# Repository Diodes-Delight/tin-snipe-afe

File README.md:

# Tin Snipe Analog Frontend

Tin Snipe is a multimeter for the hardware engineer on the go.

More to follow.

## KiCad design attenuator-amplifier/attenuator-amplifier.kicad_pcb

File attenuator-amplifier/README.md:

# Attenuator and Amplifier

This project is the attenuator and the amplifier portion of the AFE.
The attenuation is 1000:1, 100:1 and 10:1 while the amplification can be set to 1x, 10x and 100x with the 1x being the buffer
configuration which is used for signals which are either exactly in range or for attenuated signals which should also be buffered
so as to not load the input source too much.

## Building the firmware

The board itself does not contain any microcontrollers, but for testing a TI LaunchPad LP-MSPM0C1104 is used. This board was chosen for its low cost, wide availability from distributors and on board debugger.

For building and running, [Code Composer Studio](https://www.ti.com/tool/CCSTUDIO) and the [LP-MSPM0C1104](https://www.ti.com/tool/LP-MSPM0C1104) are necessary.
To build and run the firmware, simply open this folder in ccstudio and either use the Menu Run->Flash Project or Debug Project. ccstudio automatically detects the plugged in LaunchPad and can debug and flash the system from within the IDE.

The connectors J4 and J5 should be connected with cables in order to the following pins:

```
J4:

1 - PA25
2 - PA26
3 - PA17
4 - PA6
5 - PA11
6 - PA24
7 - PA4
8 - GND

J5:

1 - read below
2 - 3.3V
2 - unused for now
4 - GND
```

Warning! connect pin 1 to 5V only after the board has been flashed at least once! This is to prevent it being in an undefined state and potentially damaging the relays.

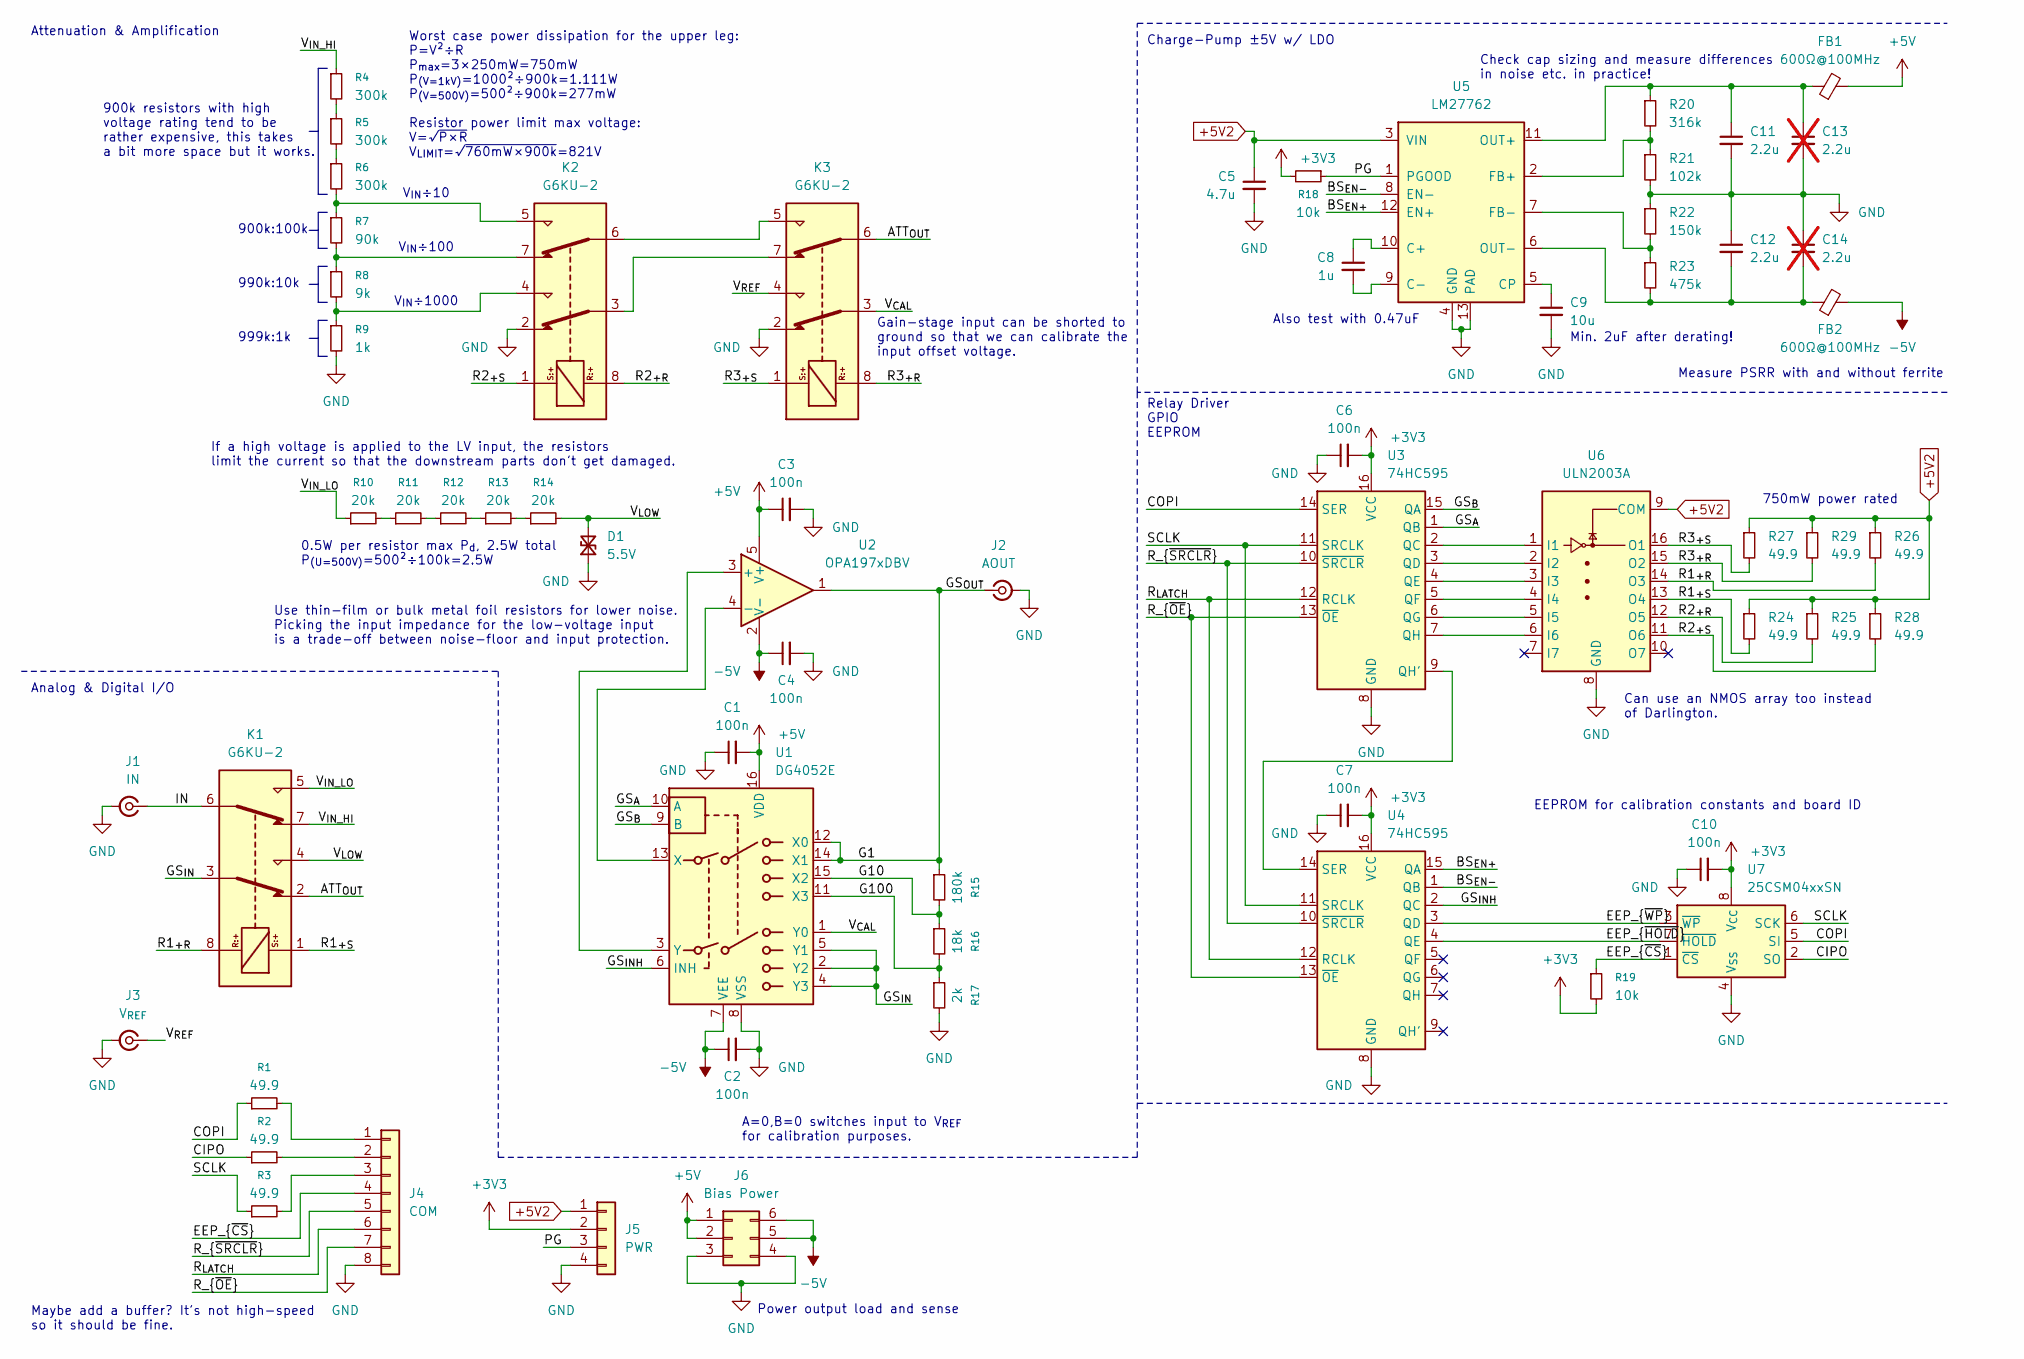
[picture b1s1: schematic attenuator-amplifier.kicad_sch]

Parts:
C1, C2, C3, C4, C6, C7, C10: 100n; C_0402_1005Metric; MPN FN15X104K500PKG
C5: 4.7u; C_0603_1608Metric; MPN TCC0603X7R475K100CT
C8: 1u; C_0603_1608Metric; MPN CGA0603X7R105K250JT
C9: 10u; C_0603_1608Metric; MPN GRM188Z71A106MA73D
C11, C12: 2.2u; C_0603_1608Metric; MPN GRM188Z71E225KE43D
C13, C14: 2.2u; C_0603_1608Metric; MPN GRM188Z71E225KE43D; not fitted
D1: 5.5V; D_SOD-882D; MPN PESD5V0H1BLG-QZ
FB1, FB2: 600Ω@100MHz; L_0603_1608Metric; MPN 74404024220
J1: IN; SMB_Jack_Vertical; MPN 61611002121501
J2: AOUT; SMB_Jack_Vertical; MPN 61611002121501
J3: V_{REF}; SMB_Jack_Vertical; MPN 61611002121501
J4: COM; PinSocket_1x08_P2.54mm_Vertical
J5: PWR; PinSocket_1x04_P2.54mm_Vertical
J6: Bias Power; PinHeader_2x03_P2.54mm_Vertical
K1, K2, K3: G6KU-2; Relay_DPDT_Omron_G6K-2F-Y; MPN G6KU-2F-Y-TR DC5; LCSC C2153173
R1, R2, R3: 49.9; R_0603_1608Metric; MPN 0603WAF499JT5E
R4, R5, R6: 300k; R_1206_3216Metric; MPN RT1206BRD07300KL
R7: 90k; R_1206_3216Metric; MPN RT1206BRE0790KL
R8: 9k; R_1206_3216Metric; MPN RT1206BRD079KL
R9: 1k; R_1206_3216Metric; MPN RT1206BRD071KL
R10, R11, R12, R13, R14: 20k; R_1206_3216Metric; MPN RNCP1206FTD20K0
R15: 180k; R_0603_1608Metric; MPN RT0603BRB07180KL
R16: 18k; R_0603_1608Metric; MPN RT0603BRB0718KL
R17: 2k; R_0603_1608Metric; MPN AR03BTBX2001
R18, R19: 10k; R_0603_1608Metric; MPN ARG03DTC1002
R20: 316k; R_0402_1005Metric; MPN FRC0402F3163TS
R21: 102k; R_0402_1005Metric; MPN 0402WGF1023TCE
R22: 150k; R_0402_1005Metric; MPN AECR0402F150KK9
R23: 475k; R_0402_1005Metric; MPN HPCR0402F475KK9
R24, R25, R26, R27, R28, R29: 49.9; R_1210_3225Metric; MPN HP0707F499JT5E; LCSC C2759009
U1: DG4052E; SOIC-16_3.9x9.9mm_P1.27mm; MPN DG4052EEY-T1-GE3
U2: OPA197xDBV; SOT-23-5; MPN OPA197IDBVT
U3, U4: 74HC595; SOIC-16_3.9x9.9mm_P1.27mm; MPN SN74HCS595
U5: LM27762; WSON-12-1EP_3x2mm_P0.5mm_EP1x2.65_ThermalVias; MPN LM27762DSSR
U6: ULN2003A; SOIC-16_3.9x9.9mm_P1.27mm; MPN ULN2003ADR
U7: 25CSM04xxSN; SOIC-8_3.9x4.9mm_P1.27mm; MPN FT25C32A-USR-T

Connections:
+3V3: C6.2, C7.2, C10.2, J5.2, R18.2, R19.2, U3.16 (VCC), U4.16 (VCC), U7.8 (V_{CC})
+5V: C1.2, C3.1, FB1.2, J6.1, J6.2, U1.16 (VDD), U2.5 (V+)
+5V2: C5.1, J5.1, R24.1, R25.1, R26.1, R27.1, R28.1, R29.1, U5.3 (VIN), U6.9 (COM)
-5V: C2.1, C4.1, FB2.2, J6.5, J6.6, U1.7 (VEE), U2.2 (V-)
/ATT_{OUT}: K1.2, K3.6
/BS_{EN+}: U4.15 (QA), U5.12 (EN+)
/BS_{EN-}: U4.1 (QB), U5.8 (EN-)
/CIPO: R2.1, U7.2 (SO)
/COPI: R1.1, U3.14 (SER), U7.5 (SI)
/EEP_{~CS}: J4.4, R19.1, U7.1 (~CS)
/EEP_{~HOLD}: U4.4 (QE), U7.7 (~HOLD)
/EEP_{~WP}: U4.3 (QD), U7.3 (~WP)
/G1: J2.1 (In), R15.1, U1.12 (X0), U1.14 (X1), U2.1
/G10: R15.2, R16.1, U1.15 (X2)
/G100: R16.2, R17.1, U1.11 (X3)
/GS_{A}: U1.10 (A), U3.1 (QB)
/GS_{B}: U1.9 (B), U3.15 (QA)
/GS_{INH}: U1.6 (INH), U4.2 (QC)
/GS_{IN}: K1.3, U1.2 (Y2), U1.4 (Y3), U1.5 (Y1)
/IN: J1.1 (In), K1.6
/PG: J5.3, R18.1, U5.1 (PGOOD)
/R1_{+R}: K1.8, R26.2, U6.14 (O3)
/R1_{+S}: K1.1, R24.2, U6.13 (O4)
/R2_{+R}: K2.8, R25.2, U6.12 (O5)
/R2_{+S}: K2.1, R28.2, U6.11 (O6)
/R3_{+R}: K3.8, R29.2, U6.15 (O2)
/R3_{+S}: K3.1, R27.2, U6.16 (O1)
/R_{LATCH}: J4.6, U3.12 (RCLK), U4.12 (RCLK)
/R_{~OE}: J4.7, U3.13 (~OE), U4.13 (~OE)
/R_{~SRCLR}: J4.5, U3.10 (~SRCLR), U4.10 (~SRCLR)
/SCLK: R3.1, U3.11 (SRCLK), U4.11 (SRCLK), U7.6 (SCK)
/V_{CAL}: K3.3, U1.1 (Y0)
/V_{IN_HI}: K1.7, R4.1
/V_{IN_LO}: K1.5, R10.1
/V_{LOW}: D1.2 (A2), K1.4, R14.2
/V_{REF}: J3.1 (In), K3.4
GND: C1.1, C2.2, C3.2, C4.2, C5.2, C6.1, C7.1, C9.2, C10.1, C11.2, C12.1, C13.2, C14.1, D1.1 (A1), J1.2 (Ext), J2.2 (Ext), J3.2 (Ext), J4.8, J5.4, J6.3, J6.4, K2.2, K3.2, R9.2, R17.2, R21.2, R22.1, U1.8 (VSS), U3.8 (GND), U4.8 (GND), U5.4 (GND), U5.13 (PAD), U6.8 (GND), U7.4 (V_{SS})
unnamed: J4.1, R1.2
unnamed: J4.2, R2.2
unnamed: J4.3, R3.2
unnamed: K2.3, K3.7
unnamed: K2.4, R8.2, R9.1
unnamed: K2.5, R6.2, R7.1
unnamed: K2.6, K3.5
unnamed: K2.7, R7.2, R8.1
unnamed: R4.2, R5.1
unnamed: R5.2, R6.1
unnamed: R10.2, R11.1
unnamed: R11.2, R12.1
unnamed: R12.2, R13.1
unnamed: R13.2, R14.1
unnamed: U1.13 (X), U2.4 (-)
unnamed: U1.3 (Y), U2.3 (+)
unnamed: U3.2 (QC), U6.1 (I1)
unnamed: U3.3 (QD), U6.2 (I2)
unnamed: U3.4 (QE), U6.3 (I3)
unnamed: U3.5 (QF), U6.4 (I4)
unnamed: U3.6 (QG), U6.5 (I5)
unnamed: U3.9 (QH'), U4.14 (SER)
unnamed: U3.7 (QH), U6.6 (I6)
unnamed: C8.1, U5.10 (C+)
unnamed: C8.2, U5.9 (C-)
unnamed: C9.1, U5.5 (CP)
unnamed: R20.2, R21.1, U5.2 (FB+)
unnamed: R22.2, R23.1, U5.7 (FB-)
unnamed: C11.1, C13.1, FB1.1, R20.1, U5.11 (OUT+)
unnamed: C12.2, C14.2, FB2.1, R23.2, U5.6 (OUT-)

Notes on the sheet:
Gain-stage input can be shorted to ground so that we can calibrate the input offset voltage.
Relay Driver GPIO EEPROM
Attenuation & Amplification
If a high voltage is applied to the LV input, the resistors limit the current so that the downstream parts don't get damaged.
Check cap sizing and measure differences in noise etc. in practice!
EEPROM for calibration constants and board ID
Power output load and sense
999k:1k
A=0,B=0 switches input to V_{REF} for calibration purposes.
V_{IN}÷100
Maybe add a buffer? It's not high-speed so it should be fine.
0.5W per resistor max P_{d}, 2.5W total P_{(U=500V)}=500²÷100k=2.5W
900k resistors with high voltage rating tend to be rather expensive, this takes a bit more space but it works.
Measure PSRR with and without ferrite
Charge-Pump ±5V w/ LDO
V_{IN}÷10
750mW power rated
Also test with 0.47uF
V_{IN}÷1000
Worst case power dissipation for the upper leg: P=V²÷R P_{max}=3×250mW=750mW P_{(V=1kV)}=1000²÷900k=1.111W P_{(V=500V)}=500²÷900k=277mW Resistor power limit max voltage: V=√~{P×R} V_{LIMIT}=√~{760mW×900k}=821V
Use thin-film or bulk metal foil resistors for lower noise. Picking the input impedance for the low-voltage input is a trade-off between noise-floor and input protection.
900k:100k
Analog & Digital I/O
990k:10k
Min. 2uF after derating!
Can use an NMOS array too instead of Darlington.

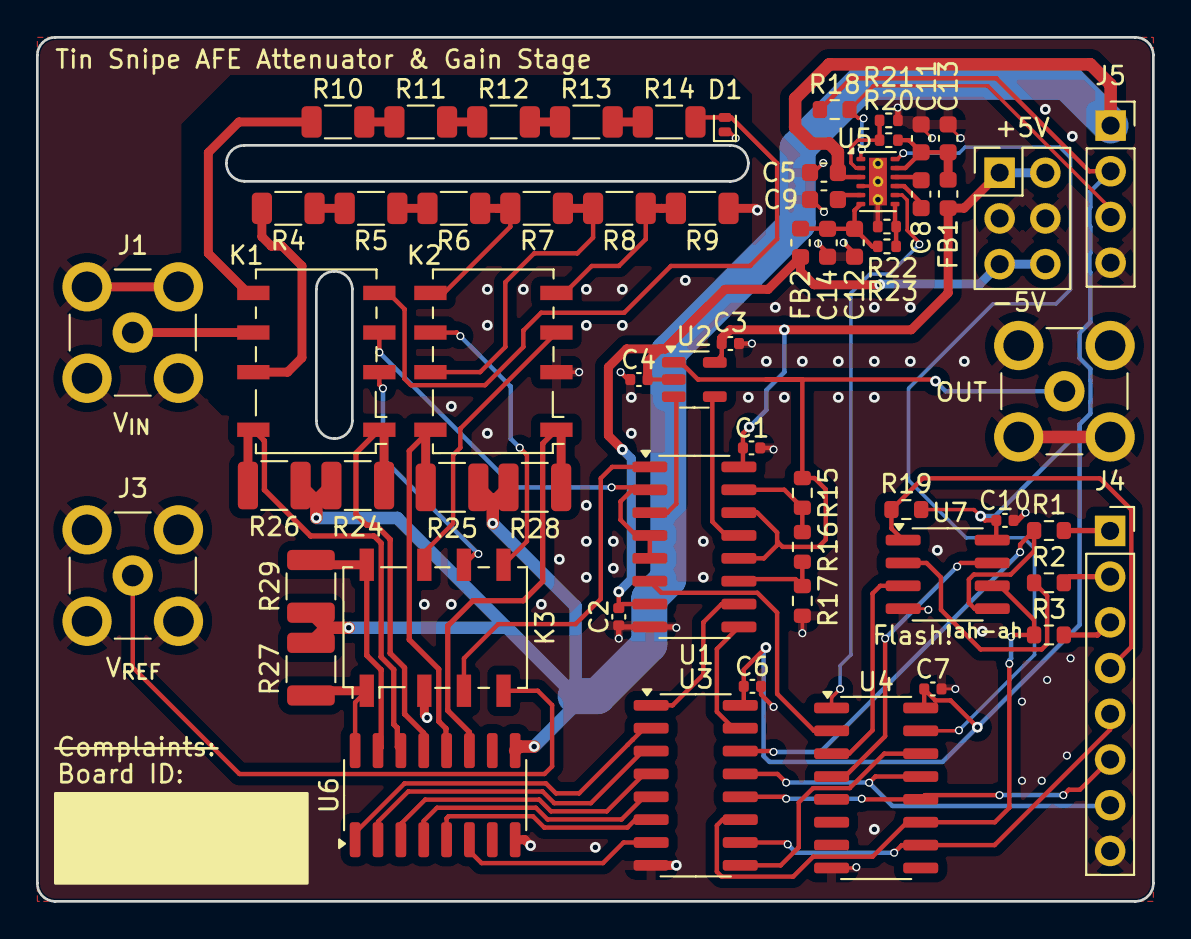
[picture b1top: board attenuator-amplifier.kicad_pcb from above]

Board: 4 copper layers, 62.0 x 48.0 mm, 62 parts (0 on the bottom side), 67 nets.

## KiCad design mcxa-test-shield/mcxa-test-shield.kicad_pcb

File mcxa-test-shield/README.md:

# FRDM-MCXA156 Test Shield

This is a mostly Arduino header compatible shield for testing the ADC of the MCXA156 and the power supplies for the OpAmps.

## Build

The programs require a working installation of the Zephyr toolchain, see the Zehpyr [Getting Started Guide](https://docs.zephyrproject.org/latest/develop/getting_started/index.html) for how to accomplish that.

With a working setup, the application can be built and flashed as follows:

```sh
# build
west build -d ../build
west flash -d ../build

# to debug
west debug -d ../build

```

## Bringup

If the program successfully flashes and the LED on the board is blinking, the LDO output voltage can be checked on the J201 pins.
The center pin is ground and the outer pins are positive and negative voltages respectively. Between the pins there should be 30V.

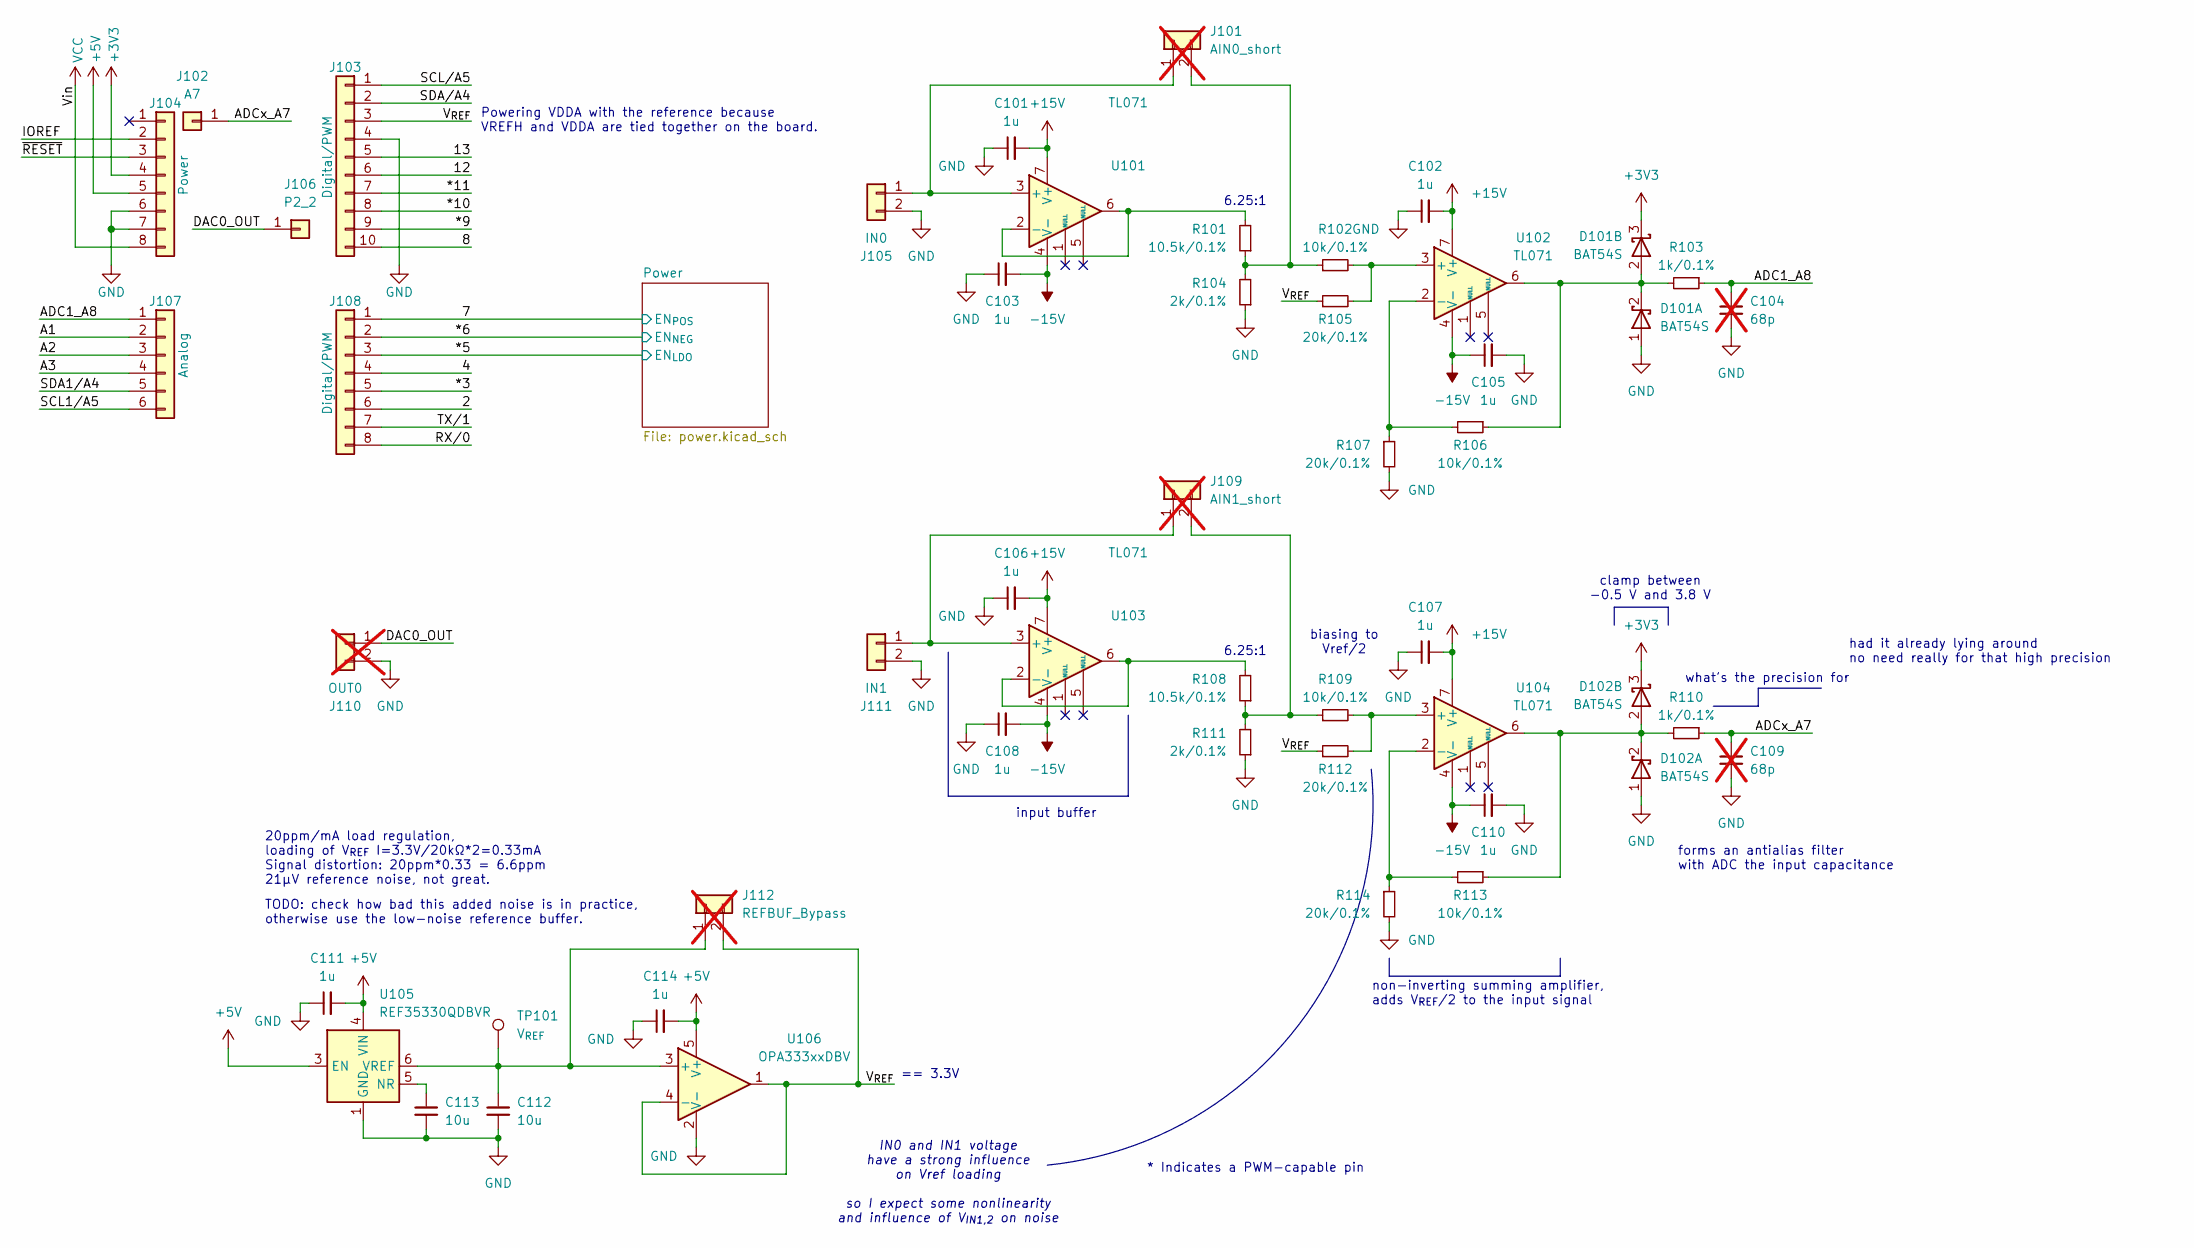
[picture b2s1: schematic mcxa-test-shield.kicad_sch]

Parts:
C101, C102, C103, C105, C106, C107, C108, C110, C111, C114: 1u; C_0402_1005Metric; MPN CL05A105KA5NQNC; LCSC C52923
C104, C109: 68p; C_0603_1608Metric; not fitted
C112, C113: 10u; C_0402_1005Metric; MPN CL05A106MQ5NUNC; LCSC C15525
D101, D102: BAT54S; SOT-23-3
J101: AIN0_short; PinHeader_1x02_P2.54mm_Vertical; not fitted
J102: A7; PinHeader_1x01_P2.54mm_Vertical
J103: Digital/PWM; PinSocket_1x10_P2.54mm_Vertical
J104: Power; PinSocket_1x08_P2.54mm_Vertical
J105: IN0; PinHeader_1x02_P2.54mm_Vertical
J106: P2_2; PinHeader_1x01_P2.54mm_Vertical
J107: Analog; PinSocket_1x06_P2.54mm_Vertical
J108: Digital/PWM; PinSocket_1x08_P2.54mm_Vertical
J109: AIN1_short; PinHeader_1x02_P2.54mm_Vertical; not fitted
J110: OUT0; PinHeader_1x02_P2.54mm_Vertical; not fitted
J111: IN1; PinHeader_1x02_P2.54mm_Vertical
J112: REFBUF_Bypass; PinHeader_1x02_P2.54mm_Vertical; not fitted
R101, R108: 10.5k/0.1%; R_0603_1608Metric; MPN PTFR0603B10K5N9; LCSC C2692889
R102, R106, R109, R113: 10k/0.1%; R_0603_1608Metric; MPN RT0603BRD0710KL; LCSC C95204
R103, R110: 1k/0.1%; R_0603_1608Metric; MPN AR03BTB1001; LCSC C408913
R104, R111: 2k/0.1%; R_0603_1608Metric; MPN PTFR0603B2K00N9; LCSC C394539
R105, R107, R112, R114: 20k/0.1%; R_0603_1608Metric; MPN RT0603BRD0720KL; LCSC C723637
TP101: V_{REF}; TestPoint_Pad_D1.5mm
U101, U102, U103, U104: TL071; SOIC-8_3.9x4.9mm_P1.27mm
U105: REF35330QDBVR; SOT-23-6
U106: OPA333xxDBV; SOT-23-5

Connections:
+3V3: D101.3 (K), D102.3 (K), J104.4
+5V: C111.2, C114.2, J104.5, U105.3 (EN), U105.4 (VIN), U106.5 (V+); also elsewhere on the board
+15V: C101.2, C102.2, C106.2, C107.2, U101.7 (V+), U102.7 (V+), U103.7 (V+), U104.7 (V+); also elsewhere on the board
-15V: C103.2, C105.1, C108.2, C110.1, U101.4 (V-), U102.4 (V-), U103.4 (V-), U104.4 (V-); also elsewhere on the board
/2: J108.6
/4: J108.4
/7: J108.1; also elsewhere on the board
/8: J103.10
/12: J103.6
/13: J103.5
/*3: J108.5
/*5: J108.3; also elsewhere on the board
/*6: J108.2; also elsewhere on the board
/*9: J103.9
/*10: J103.8
/*11: J103.7
/A1: J107.2
/A2: J107.3
/A3: J107.4
/ADC1_A8: C104.1, J107.1, R103.1
/ADCx_A7: C109.1, J102.1, R110.1
/DAC0_OUT: J106.1, J110.1
/IOREF: J104.2
/RX/0: J108.8
/SCL1/A5: J107.6
/SCL/A5: J103.1
/SDA1/A4: J107.5
/SDA/A4: J103.2
/TX/1: J108.7
/V_{REF}: J103.3, J112.2, R105.1, R112.1, U106.1, U106.4 (-)
/~RESET: J104.3
GND: C101.1, C102.1, C103.1, C104.2, C105.2, C106.1, C107.1, C108.1, C109.2, C110.2, C111.1, C112.2, C113.2, C114.1, D101.1 (A), D102.1 (A), J103.4, J104.6, J104.7, J105.2, J110.2, J111.2, R104.1, R107.2, R111.1, R114.2, U105.1 (GND), U105.2 (GND), U106.2 (V-); also elsewhere on the board
unnamed: D101.2 (K), R103.2, R106.1, U102.6
unnamed: D102.2 (K), R110.2, R113.1, U104.6
unnamed: J101.1, J105.1, U101.3 (+)
unnamed: J101.2, R101.1, R102.1, R104.2
unnamed: J109.1, J111.1, U103.3 (+)
unnamed: J109.2, R108.1, R109.1, R111.2
unnamed: C112.1, J112.1, TP101.1, U105.6 (VREF), U106.3 (+)
unnamed: R101.2, U101.2 (-), U101.6
unnamed: R102.2, R105.2, U102.3 (+)
unnamed: R106.2, R107.1, U102.2 (-)
unnamed: R108.2, U103.2 (-), U103.6
unnamed: R109.2, R112.2, U104.3 (+)
unnamed: R113.2, R114.1, U104.2 (-)
unnamed: C113.1, U105.5 (NR)
VCC: J104.8

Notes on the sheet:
TODO: check how bad this added noise is in practice, otherwise use the low-noise reference buffer.
== 3.3V
6.25:1
what's the precision for
forms an antialias filter with ADC the input capacitance
IN0 and IN1 voltage have a strong influence on Vref loading so I expect some nonlinearity and influence of V_{IN1,2} on noise
non-inverting summing amplifier, adds V_{REF}/2 to the input signal
20ppm/mA load regulation, loading of V_{REF} I=3.3V/20kΩ*2=0.33mA Signal distortion: 20ppm*0.33 = 6.6ppm 21µV reference noise, not great.
input buffer
* Indicates a PWM-capable pin
biasing to Vref/2
clamp between -0.5 V and 3.8 V
had it already lying around no need really for that high precision
Powering VDDA with the reference because VREFH and VDDA are tied together on the board.

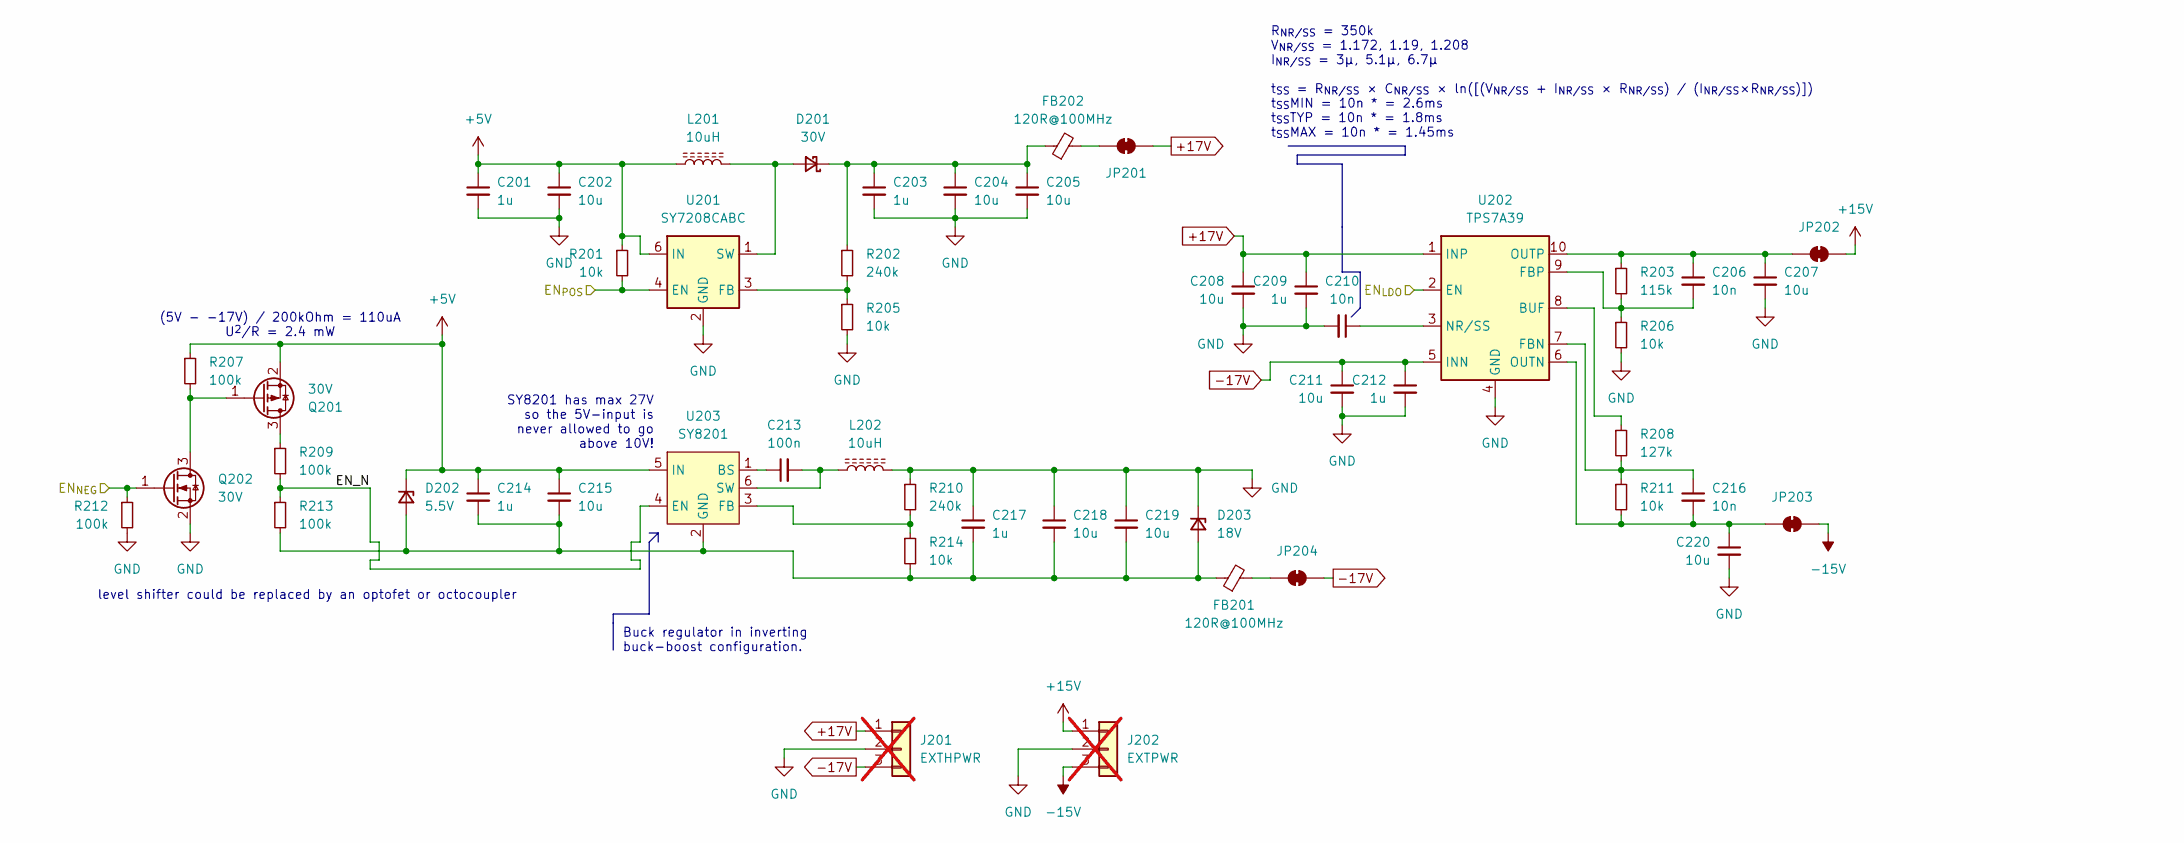
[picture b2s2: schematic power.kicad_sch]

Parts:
C201, C203, C209, C212, C214, C217: 1u; C_0402_1005Metric; MPN CL05A105KA5NQNC; LCSC C52923
C202, C204, C205, C207, C208, C211, C215, C218, C219, C220: 10u; C_0805_2012Metric; MPN GRM21BR61H106KE43L; LCSC C440198
C206, C210, C216: 10n; C_0402_1005Metric; MPN CL05B103KB5NNNC; LCSC C15195
C213: 100n; C_0402_1005Metric; MPN CL05B104KB54PNC; LCSC C307331
D201: 30V; D_SOD-123FL; MPN RB060MM-30; LCSC C308720
D202: 5.5V; D_SOD-123; MPN BZT52B5V6; LCSC C22399881
D203: 18V; D_SOD-123; MPN MM1Z18B; LCSC C22379455
FB201, FB202: 120R@100MHz; L_0603_1608Metric; MPN BLM18PG121SN1D; LCSC C14709
J201: EXTHPWR; PinHeader_1x03_P2.54mm_Vertical; not fitted
J202: EXTPWR; PinHeader_1x03_P2.54mm_Vertical; not fitted
JP201, JP202, JP204: PWR_{POS}; SolderJumper-2_P1.3mm_Bridged_RoundedPad1.0x1.5mm
JP203: PWR_{NEG}; SolderJumper-2_P1.3mm_Bridged_RoundedPad1.0x1.5mm
L201, L202: 10uH; L_Changjiang_FNR4030S; MPN FNR4030S100MT; LCSC C167879
Q201: 30V; SOT-23; MPN AO3401A; LCSC C15127
Q202: 30V; SOT-23; MPN AO3400A; LCSC C20917
R201, R205, R206, R211, R214: 10k; R_0603_1608Metric; MPN 0603WAF1002T5E; LCSC C25804
R202, R210: 240k; R_0603_1608Metric; MPN 0603WAF2403T5E; LCSC C4197
R203: 115k; R_0603_1608Metric; MPN 0603WAF1003T5E; LCSC C25803
R207, R209, R212, R213: 100k; R_0402_1005Metric; MPN 0402WGF1003TCE; LCSC C25741
R208: 127k; R_0603_1608Metric; MPN ARG03FTC1273; LCSC C217715
U201: SY7208CABC; SOT-23-6; JLC SOT-23-6
U202: TPS7A39; Texas_S-PVSON-N10_ThermalVias; MPN TPS7A3901DSCR; LCSC C2685819
U203: SY8201; SOT-23-6; MPN SY8201ABC; LCSC C108052

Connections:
+5V: C201.1, C202.1, C214.1, C215.1, D202.1 (K), L201.1, Q201.2 (S), R201.1, R207.1, U201.5 (NC), U201.6 (IN), U203.5 (IN); also elsewhere on the board
+15V: J202.1, JP202.2 (B); also elsewhere on the board
+17V: C208.1, C209.1, J201.1, JP201.2 (B), U202.1 (INP)
-15V: J202.3, JP203.2 (B); also elsewhere on the board
-17V: C211.1, C212.1, J201.3, JP204.2 (B), U202.5 (INN)
/7: R201.2, U201.4 (EN); also elsewhere on the board
/*5: U202.2 (EN); also elsewhere on the board
/*6: Q202.1 (G), R212.1; also elsewhere on the board
/Power/EN_N: R209.2, R213.1, U203.4 (EN)
GND: C201.2, C202.2, C203.2, C204.2, C205.2, C207.2, C208.2, C209.2, C210.2, C211.2, C212.2, C217.1, C218.1, C219.1, C220.2, D203.1 (K), J201.2, J202.2, L202.2, Q202.2 (S), R205.2, R206.2, R210.1, R212.2, U201.2 (GND), U202.4 (GND), U202.11 (GND); also elsewhere on the board
unnamed: D201.2 (A), L201.2, U201.1 (SW)
unnamed: C203.1, C204.1, C205.1, D201.1 (K), FB202.1, R202.1
unnamed: C214.2, C215.2, C217.2, C218.2, C219.2, D202.2 (A), D203.2 (A), FB201.1, R213.2, R214.2, U203.2 (GND)
unnamed: FB202.2, JP201.1 (A)
unnamed: C206.1, C207.1, JP202.1 (A), R203.1, U202.10 (OUTP)
unnamed: C216.2, C220.1, JP203.1 (A), R211.2, U202.6 (OUTN)
unnamed: FB201.2, JP204.1 (A)
unnamed: Q201.3 (D), R209.1
unnamed: Q201.1 (G), Q202.3 (D), R207.2
unnamed: R202.2, R205.1, U201.3 (FB)
unnamed: R208.1, U202.8 (BUF)
unnamed: C216.1, R208.2, R211.1, U202.7 (FBN)
unnamed: C206.2, R203.2, R206.1, U202.9 (FBP)
unnamed: C210.1, U202.3 (NR/SS)
unnamed: C213.1, U203.1 (BS)
unnamed: R210.2, R214.1, U203.3 (FB)
unnamed: C213.2, L202.1, U203.6 (SW)

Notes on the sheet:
Buck regulator in inverting buck-boost configuration.
R_{NR/SS} = 350k V_{NR/SS} = 1.172, 1.19, 1.208 I_{NR/SS} = 3µ, 5.1µ, 6.7µ t_{SS} = R_{NR/SS} × C_{NR/SS} × ln([(V_{NR/SS} + I_{NR/SS} × R_{NR/SS}) / (I_{NR/SS}×R_{NR/SS})]) t_{SS}MIN = 10n * = 2.6ms t_{SS}TYP = 10n * = 1.8ms t_{SS}MAX = 10n * = 1.45ms
level shifter could be replaced by an optofet or octocoupler
SY8201 has max 27V so the 5V-input is never allowed to go above 10V!
(5V - -17V) / 200kOhm = 110uA U^{2}/R = 2.4 mW

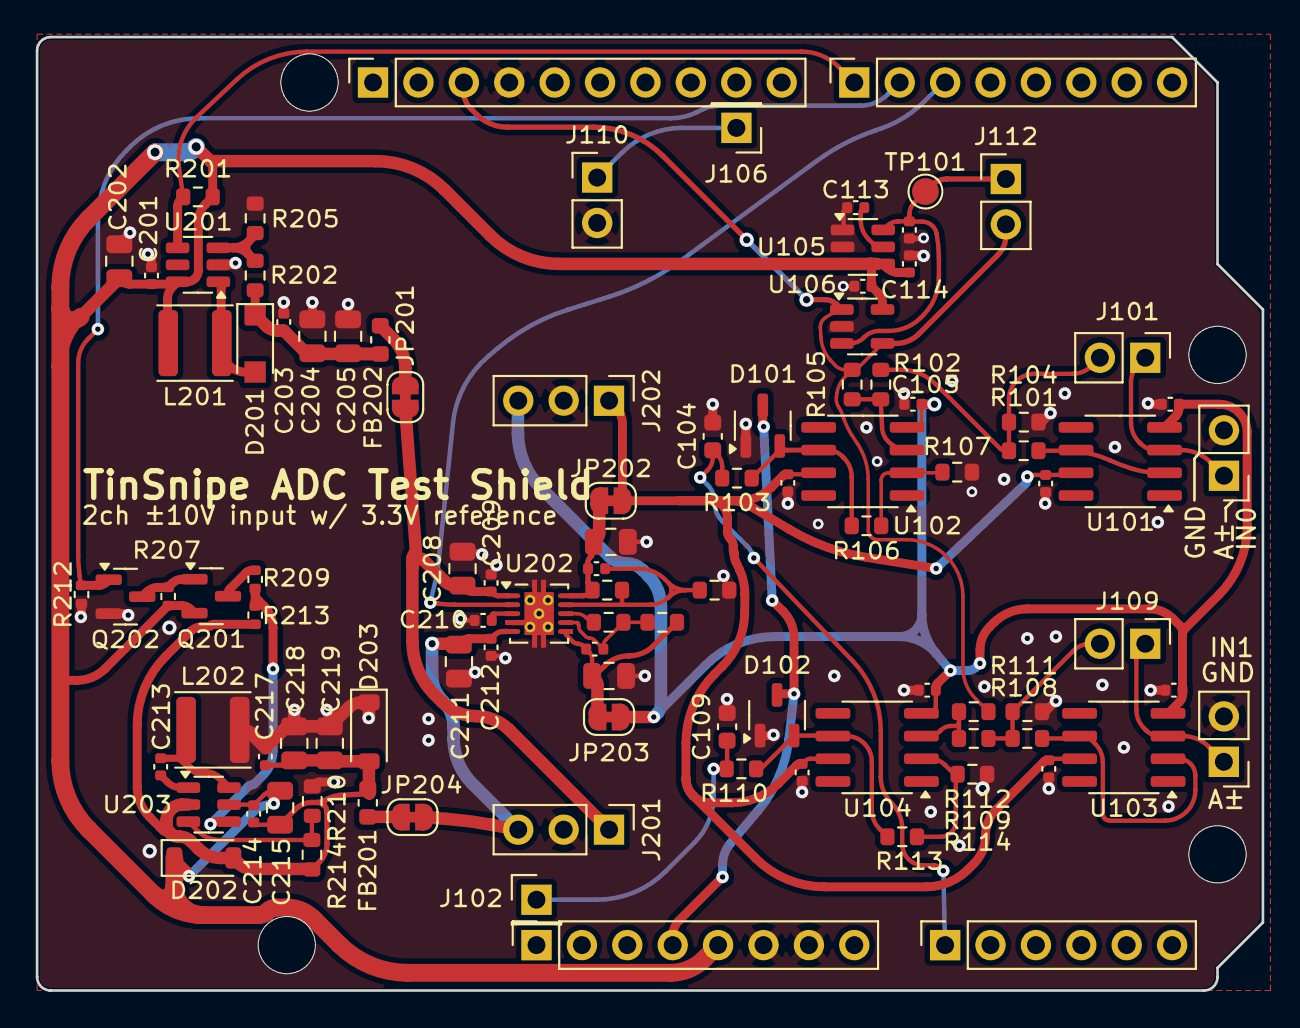
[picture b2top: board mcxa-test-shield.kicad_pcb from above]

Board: 4 copper layers, 68.6 x 53.3 mm, 104 parts (0 on the bottom side), 46 nets.

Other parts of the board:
MH1, MH2, MH3, MH4: MountingHole_3.2mm

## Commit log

2025-07-22 add input stage and power supplies test shield
2025-07-22 attenuator and amplifier draft
2025-07-23 small changes, add missing part numbers
2025-07-24 add pdf schematic for the attenuator shield too
2025-08-19 add license
2025-08-20 add basic power supply test program
2025-08-25 add initial attenuator-amplifier test code
2025-08-25 expand readme a bit more
2025-08-26 cycling through the configurations works now
2025-08-27 fix gain and attenuation switching code
